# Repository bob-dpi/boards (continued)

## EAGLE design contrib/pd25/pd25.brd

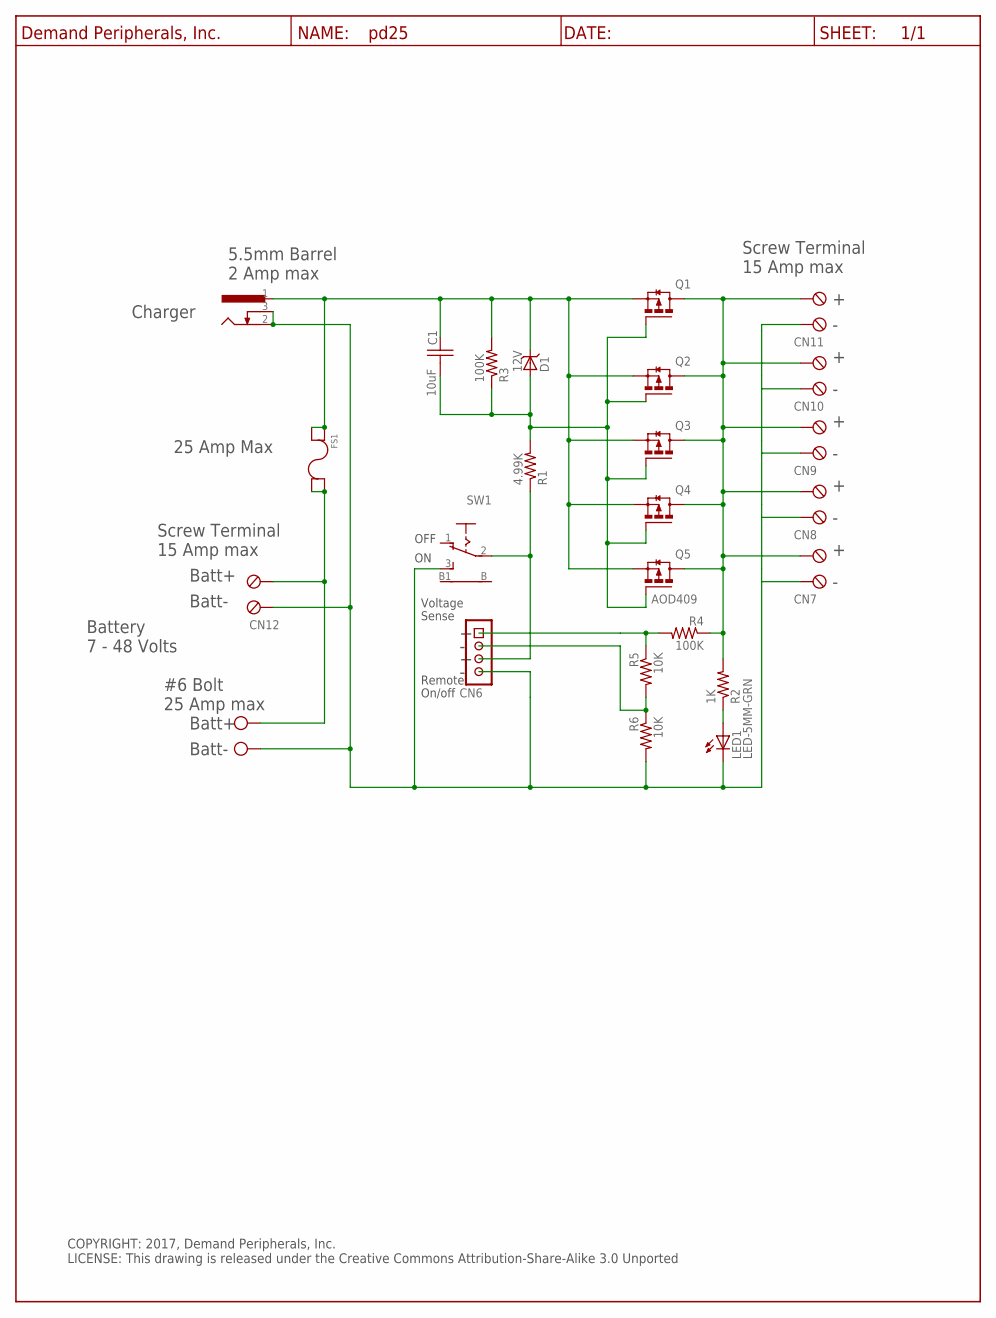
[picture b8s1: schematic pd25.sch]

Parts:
BATT+: Bolt_Connection; BOLT_6
BOLT1: Bolt_Connection; BOLT_6
C1: 10uF; C0805
CN6: HDR-4X1-LCK; HDR-4X1
CN7, CN8, CN9, CN10, CN11, CN12: TBLK-5.08-X2
D1: 12V; SOD123
FS1: FUSE-KS3557; KS3557-10
J1: Barrel-5.5mm; DC-BARREL-JACK-55MM
LED1: LED-5MM-GRN; LED5MM
Q1, Q2, Q3, Q4: FET_DPAK_P; DPACK_TO-252
Q5: AOD409; DPACK_TO-252
R1: 4.99K; R0603
R2: 1K; R0603
R3, R4: 100K; R0603
R5, R6: 10K; R0603
SW1: TOGGLE_SPDT_PC
U$1: DP_FRAME_P; P_FRAME

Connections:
BATT+: BATT+.P, CN12.2 (KL1), FS1.RS@3 (RS), FS1.RS@4 (RS)
FUSE+: C1.1, D1.C, FS1.LS@1 (LS), FS1.LS@2 (LS), J1.1, Q1.3 (S), Q2.3 (S), Q3.3 (S), Q4.3 (S), Q5.3 (S), R3.2
GND: BOLT1.P, CN6.4, CN7.1 (KL), CN8.1 (KL), CN9.1 (KL), CN10.1 (KL), CN11.1 (KL), CN12.1 (KL), J1.2, J1.3, LED1.C, R6.2, SW1.3 (S)
unnamed: LED1.A, R2.1
unnamed: CN6.1, R4.2, R5.1
unnamed: CN6.2, R5.2, R6.1
unnamed: C1.2, D1.A, Q1.1 (G), Q2.1 (G), Q3.1 (G), Q4.1 (G), Q5.1 (G), R1.2, R3.1
ON+: CN6.3, R1.1, SW1.2
V+: CN7.2 (KL1), CN8.2 (KL1), CN9.2 (KL1), CN10.2 (KL1), CN11.2 (KL1), Q1.4 (D), Q2.4 (D), Q3.4 (D), Q4.4 (D), Q5.4 (D), R2.2, R4.1

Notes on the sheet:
Batt-
Batt+
Charger
OFF
Remote
On/off
25 Amp Max
Battery
7 - 48 Volts
Voltage
Sense
Screw Terminal
15 Amp max
#6 Bolt
25 Amp max
2 Amp max
5.5mm Barrel
COPYRIGHT: 2017, Demand Peripherals, Inc. LICENSE: This drawing is released under the Creative Commons Attribution-Share-Alike 3.0 Unported

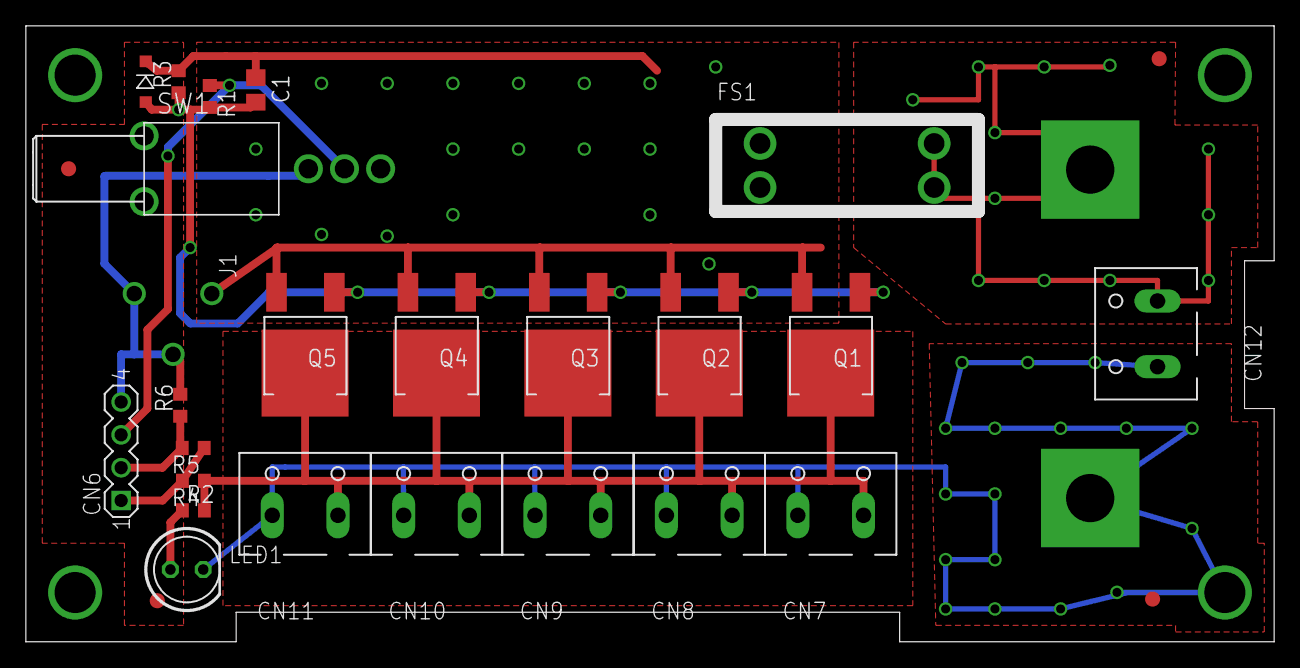
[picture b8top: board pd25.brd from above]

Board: 2 copper layers, 96.5 x 47.6 mm, 32 parts (1 on the bottom side), 9 nets.

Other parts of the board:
U$3, U$4, U$6, U$12: FIDUCIAL
U$8: DPI-2

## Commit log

2022-09-29 Added schematics to top README.md. Minor clean-up.
2022-09-29 Minor clean-up. Github markdown is not identical to grip output.
2022-10-17 Made images links on the top README.md file. Fixed a broken link.
2022-10-31 Fixed spelling errors
